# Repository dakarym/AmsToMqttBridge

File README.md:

# AMS <-> MQTT Bridge
 This project may help you build your own reader for HAN data streamed from the new AMS electrical meters installed in Norway in 2017/2018. Data is read using an Arduino-programmed ESP8266 (in an ESP12 module from AI Thinker), then pushed to MQTT over WiFi. You can have full control over this data, and you can basically do anything with it. 

 This project does not include any fancy UI setup or even storage for the AMS data.

 *Building this project will require some skills in ordering and assembling  electronic circuits as well as programming, and I have not included detailed instructions to take a beginner through the steps. I still hope some still find information here useful, maybe also for other projects.*

## Self powered HAN reader -- Work in progress

This is an update for a new self powered HAN [PCB](/PCB/KiCAD/HAN_SELF_POWERED) as originally conceived by ArnieO on the home automation [thread](https://www.hjemmeautomasjon.no/forums/topic/4933-lesing-av-amshan-uten-spenningsforsyning-the-complicated-way/).  Details on the hardware change is on the PCB [README](/PCB/README.md).  This version does not need a USB power connection.  Instead energy is taken from the HAN port connection and stored for use on the board.  A DC-DC buck converter based on the LTC3642 provides 3.3V at ~35ma from the 24V supply.  

The design has been tested and running successfully on an Aidon meter for the last 3 months.  Currently testing is pending on Kamstrup and Kafia style meters.

#### Open items / Limitations:
* The current that the buck can provide is limited to the maximum power supported by the meter HAN port.  The maximum value varies based on the meter type.  More information can be found [here](/Debugging/Documentation).  Currently the Aidon has the highest power available, but also has the fastest list frequency of 2.5 seconds.  Kamstrup and Kafia are at 10 second lists which may be beneficial as more time can be spent in low power idling.
* The most critical time for energy starvation is during the inital startup.  If the wifi or MQTT connection takes too long, the device will drop below the 2.65V cutoff for the voltage supervisor and will restart.  
* Due to this, the following edits in the [sketch](/Arduino Code/AmsToMqttBridge/AmsToMqttBridge.ino) were made:
  * Elimination of the 5 second waiting for AP time
  * Checking of the Vcc level at bootup and deepsleeping if insufficient voltage
  * Checking of the Vcc before entering the read message loop
* Fine tuning of the peak current trip threshold on the buck converter to balance average power draw with minimizing peak currents.
* Fine tuning of input current surge limiters for different meter types.  To be tested/verified soon.
  * Currently the design uses an NSI45020 as a 20 ma current clamp.  Below is a screenshot of the input surge with discharged input capacitors.  Yellow is the input current with 0.1V per ma scaling.  Cyan is input voltage.  Note the peak current clamped at ~27ma.

  * Alternatively an NPN current clamp could be used.  Such an example is shown below with the same measurements and scaling as above.  Note the peak current clamped at ~8.5ma.
  
* OTA updates will likely not be possible with this design, but will need testing
* Inital configuration of Wifi credentials and meter type will need to be done when connected to an external 3.3V supply.
* The auto reset funtionality  is implemented based on the circuit and testing of Kevin Darrah and explained [here](https://youtu.be/HdHzxM6fEig).  It is tested working on a couple of my boards with good results.

#### Next Steps:
* Test and verify on other meter types
* Respin PCB design to correct changes as needed
* Reduce cost of BOM and limited value components
* Share project on PCBWay
* Design optional case for 3d printing

## The previous hardware

*The completed board mounted in a [3D printed enclosure](/Electrical/HAN_ESP_TSS721/enclosure)*

*...installed with the electrical meter...*

*...and, showing data on a [Node Red](https://nodered.org/) dashboard*

## Background
The purpose of this project is to collect information and build a simplified bridge for reading serial DLSM/M-bus information from electrical power meters (AMS), provided over the HAN port, and publishing to some IoT friendly target.

Components will be ESP8622, Arduino code and an M-bus <-> 3.3V serial interface

As a start, we should try to get information from the three types of AMS meters currently being installed in Norway. Some details about these are available here: [NVE_Info_kunder_HANgrensesnitt.pdf](./Debugging/Documentation/NVE_Info_kunder_HANgrensesnitt.pdf)

Quite some work was put into parse and guess how the data protocol was defined. Unfortunately, I did not have access to the (rather expensive) standardization documentation, but with some collaborative effort we solved most details.

### This project includes

- [X] [Circuit to read MBus data, parse the DSLM and report to MQTT over WiFi](./PCB/KiCAD/HAN_ESP_TSS721)
- [X] [Code to capture and analyze data from a PC](./Debugging/Code/HanDebugger)
- [X] [Code to capture and analyze data from Arduino](./Debugging/Code/ESPDebugger)
- [X] [Sample data from various meters](./Debugging/Samples)
- [X] [Documentation on HAN / MBus / DLMS/COSEM](./Debugging/Documentation)
- [X] [Code to parse DLMS data into a structure](./Arduino%20Code/Arduino%20Libraries/HanReader/src)
- [X] [Real schematics, including ESP8266](./PCB/KiCAD/HAN_ESP_TSS721#schematics)
- [X] [PCB layout](./PCB/KiCAD/HAN_ESP_TSS721#pcb)
- [X] [Component list](./PCB/KiCAD/HAN_ESP_TSS721#componenet-list)
- [X] [Arduino library](./Arduino%20Code)
- [X] [Complete Arduino sketch to read values and report to MQTT server](./Arduino%20Code/AmsToMqttBridge)

[The completed project](./Arduino%20Code/AmsToMqttBridge) also includes:

- Boot as Access Point and web server to allow config from a web browser. This allows you to set SSID, password, MQTT server and port, as well as topics for publish and subscribe
- On-board temperature sensor, also reported in json to MQTT

## Electrical design

The [most recent design](/PCB/KiCAD/HAN_ESP_TSS721) uses an [ESP8266](http://esp8266.net/) in an ESP12 module from [AI Thinker](https://www.ai-thinker.com) for micro processing and the [TSS721](http://www.ti.com/product/TSS721A) from Texas Instruments for level conversion from M-Bus to TTL (3.3V). An earlier design solved the level conversion using an op-amp, which might be an easier and more available solution, but also more error-prone. See more details in [electrical design](./Electrical).

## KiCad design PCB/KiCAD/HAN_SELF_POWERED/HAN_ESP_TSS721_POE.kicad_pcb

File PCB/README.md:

# Overview

Here are links to the different board designs together with a short summary.

## HAN_SELF_POWERED (Self contained and HAN Powered)

This [board](HAN_SELF_POWERED) contains a built in power supply to run without any external connection.  It is an evolution of the design proposed by ArnieO on the home automation forum [thread](https://www.hjemmeautomasjon.no/forums/topic/4933-lesing-av-amshan-uten-spenningsforsyning-the-complicated-way/).

Noteable changes from the below boards are:
* Uses [LTC3642](https://www.analog.com/media/en/technical-documentation/data-sheets/3642fc.pdf) for power delivery from the HAN signals
* Current limiter for preventing inrush tripping of overcurrent on HAN reader
* Voltage supervisor circuit via [TPS3808](http://www.ti.com/lit/ds/symlink/tps3808.pdf) for controlled ESP startup
* New layout with surface mount components and reduced size

Building notes:
* JP2 must be closed to enable recovery from deep sleep mode.  This is required.
* The EPS Prog/Reset circuitry is optional as the board can be programmed via the PROG and RST buttons.
* MRST button is optional, it forces a clean delay of the ESP reset.
* C7 is shown as a capacitor, but the latest version is a resistor value instead.  Next version will move to a resistor symbol.
* C6 can be omitted if desired.
* R1, R2 and R6 build custom hystersis for the TPS3808 based on [this](http://www.ti.com/lit/an/slva360/slva360.pdf) application note.

A (mostly) assembled prototype board is shown here:

## HAN_ESP_TSS721 (USB Powered)

This is the current and most robust design for the [main board](HAN_ESP_TSS721). There's been great help in creating this, both here on GitHub, but also at the Norwegian home automation forum, [www.hjemmeautomasjon.no](https://www.hjemmeautomasjon.no/forums/topic/1982-lesing-av-ams-data-amshan-iot/)

The board

* uses TSS721 for MBus to TTL conversion
* holds ESP8266 for processing and transmit HAN data to WiFi / MQTT
* full schematics and PCB in editable [KiCad](http://www.kicad-pcb.org/) source files
* features a temperature sensor (DS18B20)
* uses a modular design, leaving these features optional
  * temperature sensor
  * M-bus TX
  * WiFi (Leave ESP, power supply and use for only M-bus to TTL)

### Status

At the time of this writing, this has never been tried as a whole, but all parts has been prototyped individually. First PCB prototypes are very soon in the order.

## HAN_ESP_Simple (Was: Board 1)

The project's original [board design](HAN_ESP_Simple). It

* is based on the ESP8266 chip
* is powered by USB
* uses a very simple voltage divider to demodulate the M-bus signal
* has shematic and pcb design only available as finished pdf/png files

### Status

Prototypes have been made and some people have started using them(?).

## HAN_TTL_TSS721 (Was: Board 2)

This [board design](HAN_TTL_TSS721) is a newer alternative to the original. It

* is an Arduino shield.
* uses the industry standard TSS721 chip to interface the M-bus.
* is optically isolate
* has shematic and pcb design available in editable [KiCad](http://www.kicad-pcb.org/) source files

### Status

Unfinished, just started.

## MBUS_Simulator (Was: Board 3)

This [board](MBUS_Simulator) is a M-bus master simulator to be able to develop and
test the other boards without being dependent on having and using a real AMS unit.

### Status

Implementation done.

Please also see [Getting started building or modifying](GETTING_STARTED.md)

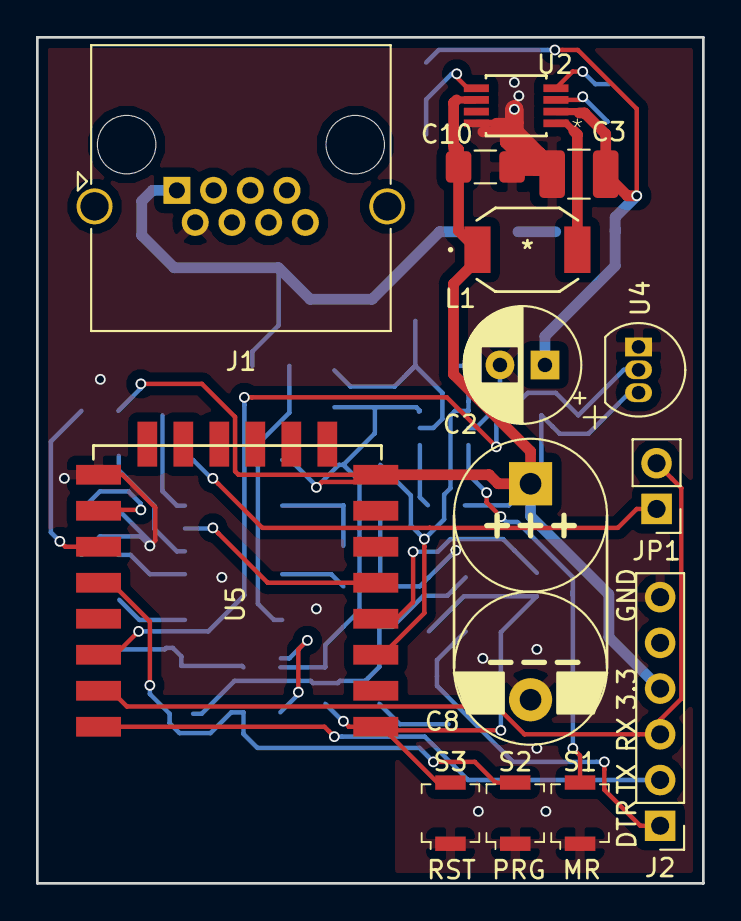
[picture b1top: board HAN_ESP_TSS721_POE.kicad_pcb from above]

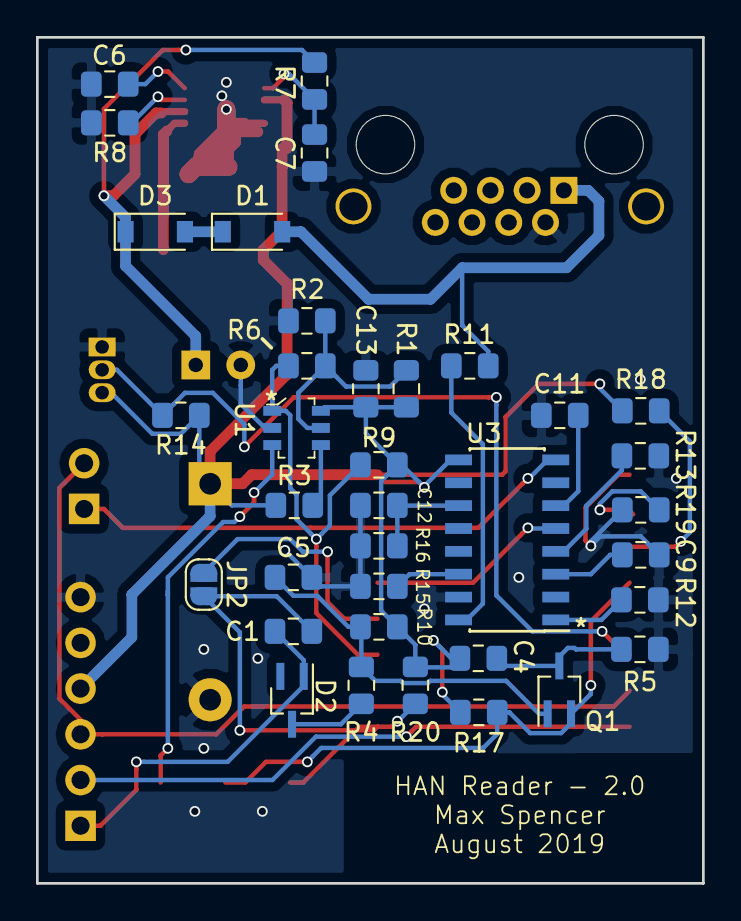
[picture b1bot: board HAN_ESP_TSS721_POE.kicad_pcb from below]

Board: 2 copper layers, 37.0 x 47.0 mm, 50 parts (36 on the bottom side), 34 nets.

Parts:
C1, C4, C5: 10u; C_0805_2012Metric_Pad1.15x1.40mm_HandSolder
C2: 33u; CP_Radial_D6.3mm_P2.50mm
C3: 10u; C_1210_3225Metric_Pad1.42x2.65mm_HandSolder
C6: 1p; C_0805_2012Metric_Pad1.15x1.40mm_HandSolder
C7: 500n; C_0805_2012Metric_Pad1.15x1.40mm_HandSolder
C8: 1; DGH105Q5R5_17mm_8.5mm_12mmP
C9: 1u; C_0805_2012Metric_Pad1.15x1.40mm_HandSolder
C10: 47u; C_1206_3216Metric_Pad1.42x1.75mm_HandSolder
C11, C12: 100n; C_0805_2012Metric_Pad1.15x1.40mm_HandSolder
C13: .1u; C_0805_2012Metric_Pad1.15x1.40mm_HandSolder
D1: MBR130T1G; D_SOD-123
D2: BAT54ADW; SOT-323_SC-70_Handsoldering
D3: NSI45020; D_SOD-123
J1: RJ45_Shielded; RJ45_Amphenol_RJHSE5380
J2: FTDI; Pin_Header_Straight_1x06_Pitch2.54mm
JP1: RX; Pin_Header_Straight_1x02_Pitch2.54mm
JP2: SolderJumper_2_Open; SolderJumper-2_P1.3mm_Open_RoundedPad1.0x1.5mm
L1: SRR6603-220ML
Q1: MMBT2907AWT1G; SOT-323_SC-70_Handsoldering
R1: 220k; R_0805_2012Metric_Pad1.15x1.40mm_HandSolder
R2: 33k; R_0805_2012Metric_Pad1.15x1.40mm_HandSolder
R3, R16: 100k; R_0805_2012Metric_Pad1.15x1.40mm_HandSolder
R4, R5: 100; R_0805_2012Metric_Pad1.15x1.40mm_HandSolder
R6, R7: 1M; R_0805_2012Metric_Pad1.15x1.40mm_HandSolder
R8: 600k; R_0805_2012Metric_Pad1.15x1.40mm_HandSolder
R9, R10, R17, R18, R19, R20: 10k; R_0805_2012Metric_Pad1.15x1.40mm_HandSolder
R11, R12: 220R; R_0805_2012Metric_Pad1.15x1.40mm_HandSolder
R13: 30k; R_0805_2012Metric_Pad1.15x1.40mm_HandSolder
R14: 4k7; R_0805_2012Metric_Pad1.15x1.40mm_HandSolder
R15: 470R; R_0805_2012Metric_Pad1.15x1.40mm_HandSolder
S1, S2, S3: B3U-1000P; Switch_Tactile_SMD_B3U-1000P
U1: TPS3808G01DBVR; SOT-23-6
U2: LTC3642IMS8EPBF; MSOP-8_MS
U3: TSS721; SOIC-16_3.9x9.9mm_Pitch1.27mm
U4: DS18B20; TO-92_Inline
U5: ESP-12E; ESP-12E_SMD

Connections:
+3V3: C4.1, C8.1, C10.1, C13.2, J2.4, L1.1, R1.2, R3.1, R9.1, R10.1, R14.1, R17.1, R18.2, R20.2, U1.6, U2.6, U3.9, U4.3, U5.8
CH_PD: R6.1, R9.2, U1.1, U5.3
DTR: C1.2, D2.1, J2.1
ESP_PROG: Q1.2, R17.2, S2.2, U5.12
ESP_RESET: C1.1, JP2.2, R20.1, S3.2, U5.1
ESP_RX: J2.3, JP1.2, U5.15
ESP_TX: J2.2, U5.16
ESP_Temp: R14.2, U4.2, U5.14
GND: C2.2, C3.2, C5.2, C6.2, C7.1, C8.2, C9.2, C10.2, C11.2, C12.2, C13.1, J1.2, J2.6, R2.2, R5.2, R8.2, R12.2, R13.2, R15.2, R16.1, R19.1, S1.1, S2.1, S3.1, U1.2, U2.8, U3.15, U4.1, U5.9
HAN1: D1.2, J1.1, R11.1
HAN_TX: JP1.1, U3.8
MR: S1.2, U1.3
unnamed: C2.1, C3.1, D3.1, R7.1, U2.2
unnamed: C4.2, Q1.3, R5.1
unnamed: C5.1, Q1.1, R4.1, R10.2
unnamed: C6.1, U2.4
unnamed: C7.2, R7.2, U2.5
unnamed: C9.1, U3.3
unnamed: C11.1, U3.6
unnamed: C12.1, R16.2, U3.11
unnamed: D1.1, D3.2
unnamed: D2.3, R4.2
unnamed: JP2.1, U5.4
unnamed: L1.2, U2.1
unnamed: R1.1, R2.1, R6.2, U1.5
unnamed: R3.2, U1.4
unnamed: R8.1, U2.3
unnamed: R11.2, U3.16
unnamed: R12.1, U3.1
unnamed: R13.1, U3.4
unnamed: R15.1, U3.14
unnamed: R18.1, U5.11
unnamed: R19.2, U5.10
POWER_FAIL: U3.5, U5.5

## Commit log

2019-10-28 Added original Kicad files for self powered board
2019-10-28 Updates to schematic R7, C7, U2, C13, R13, U3
2019-10-28 Edits to sketch for vcc check and reporting
2019-10-28 Added screenshots and pictures
2019-10-28 Update README.md
    First notes on self powered PCB
2019-10-28 Update README.md
    Updated for self powered board option
2019-11-11 added same return function for list handlers with short lists
2019-11-14 Update readme with auto reset testing
    Auto reset was tested and is working as expected!

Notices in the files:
parts and their libraries:
Copyright 2016 Accelerated Designs. All rights reserved.
